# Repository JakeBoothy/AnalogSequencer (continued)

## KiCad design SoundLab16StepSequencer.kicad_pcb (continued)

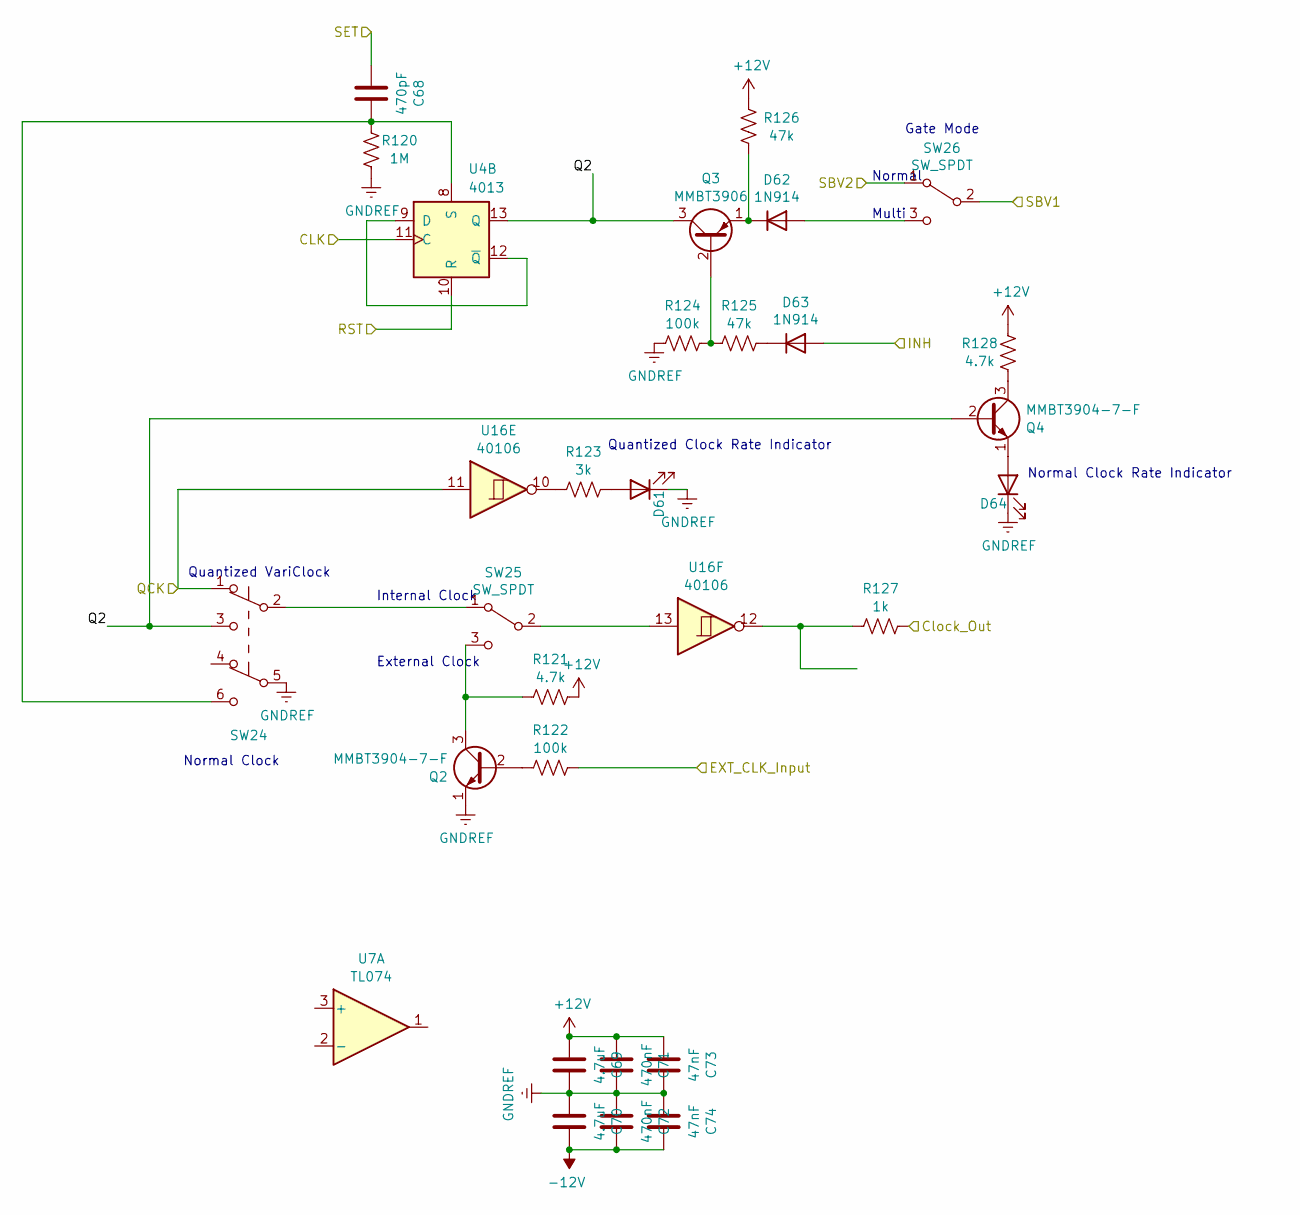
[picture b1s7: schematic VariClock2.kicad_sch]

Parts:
C68: 470pF; C_0603_1608Metric
C69, C70: 4.7uF; C_0805_2012Metric
C71, C72: 470nF; C_0805_2012Metric
C73, C74: 47nF; C_0603_1608Metric
D61, D64: LED; LED_D5.0mm
D62, D63: 1N914; D_SOD-323F
Q2, Q4: MMBT3904-7-F; SOT-23-3
Q3: MMBT3906; SOT-23-3
R120: 1M; R_0603_1608Metric
R121, R128: 4.7k; R_0603_1608Metric
R122, R124: 100k; R_0603_1608Metric
R123: 3k; R_0603_1608Metric
R125, R126: 47k; R_0603_1608Metric
R127: 1k; R_0603_1608Metric
SW24: SW_Push_DPDT; MTS-203-A1-T0
SW25, SW26: SW_SPDT; MTS-103-A01-T0
U4: 4013; SOIC-14_3.9x8.7mm_P1.27mm
U7: TL074; SO-14_3.9x8.65mm_P1.27mm
U16: 40106; SOIC-14_3.9x8.7mm_P1.27mm

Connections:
+12V: C69.2, C71.2, C73.2, R121.2, R126.2, R128.2; also elsewhere on the board
-12V: C70.1, C72.1, C74.1; also elsewhere on the board
/SequencerClocking/X2: D63.2 (A); also elsewhere on the board
/SequencerInput/SBV1: SW26.2 (B); also elsewhere on the board
/SequencerInput/SBV2: SW26.1 (A); also elsewhere on the board
/VariClock1/CLK: U4.11 (C); also elsewhere on the board
/VariClock1/QCK: SW24.1 (A), U16.11; also elsewhere on the board
/VariClock1/RST: U4.10 (R); also elsewhere on the board
/VariClock1/SET: C68.2; also elsewhere on the board
/VariClock2/Clock_Out: R127.2; also elsewhere on the board
/VariClock2/EXT_CLK_Input: R122.2; also elsewhere on the board
/VariClock2/Q2: Q3.3 (C), Q4.2 (B), SW24.3 (C), U4.13 (Q)
GNDREF: C69.1, C70.2, C71.1, C72.2, C73.1, C74.2, D61.1 (K), D64.1 (K), Q2.1 (E), R120.2, R124.1, SW24.5 (B); also elsewhere on the board
unnamed: D61.2 (A), R123.2
unnamed: D62.2 (A), SW26.3 (C)
unnamed: D62.1 (K), Q3.1 (E), R126.1
unnamed: D63.1 (K), R125.2
unnamed: D64.2 (A), Q4.1 (E)
unnamed: Q2.2 (B), R122.1
unnamed: Q2.3 (C), R121.1, SW25.3 (C)
unnamed: Q3.2 (B), R124.2, R125.1
unnamed: Q4.3 (C), R128.1
unnamed: R123.1, U16.10
unnamed: R127.1, U16.12
unnamed: SW24.2 (B), SW25.1 (A)
unnamed: SW25.2 (B), U16.13
unnamed: U4.9 (D), U4.12 (~Q)
unnamed: C68.1, R120.1, SW24.6 (C), U4.8 (S)

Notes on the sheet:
Normal
Normal Clock
Quantized VariClock
External Clock
Quantized Clock Rate Indicator
Normal Clock Rate Indicator
Multi
Gate Mode
Internal Clock

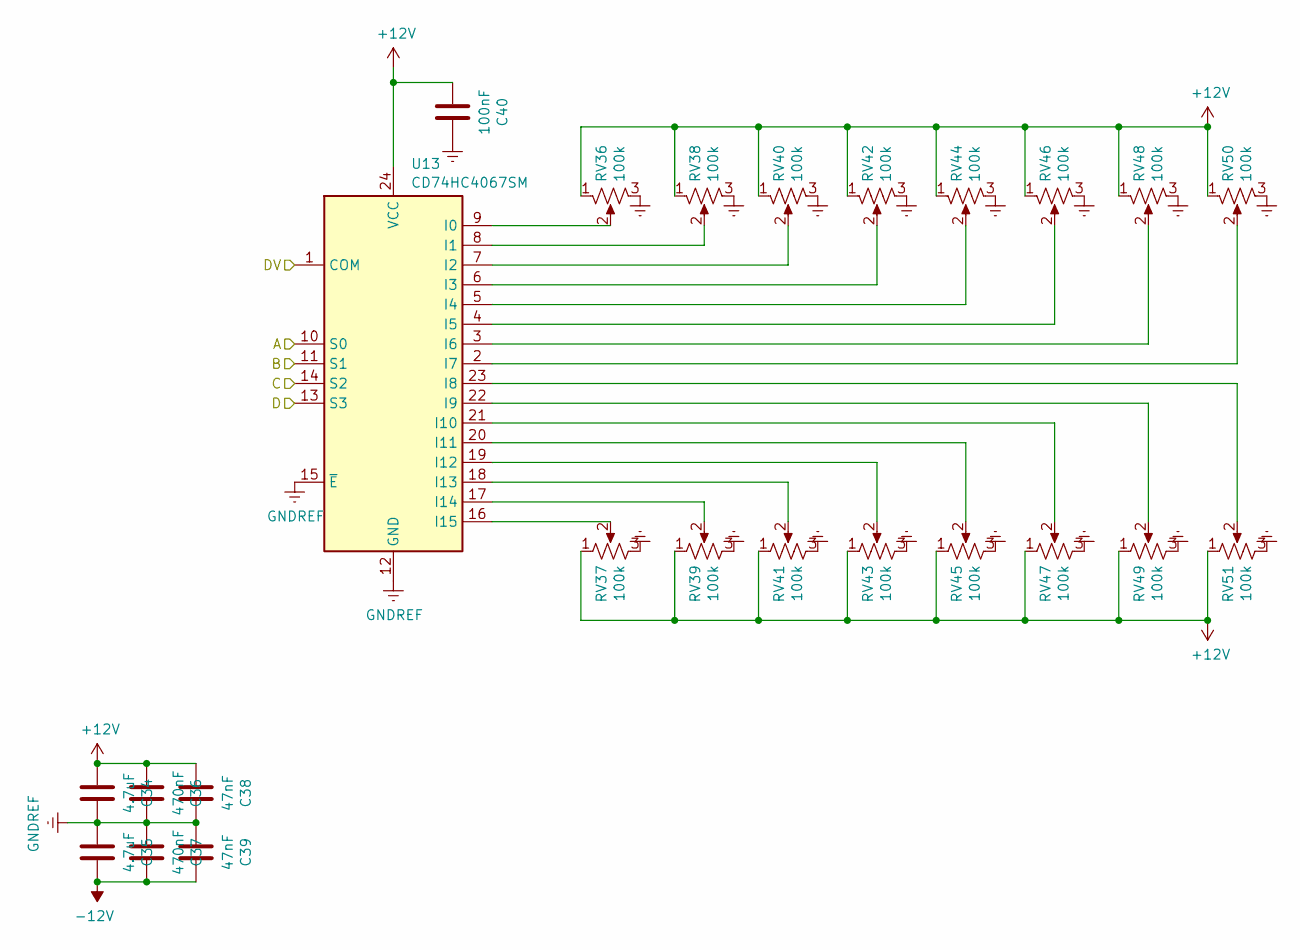
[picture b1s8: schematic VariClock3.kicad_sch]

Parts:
C34, C35: 4.7uF; C_0805_2012Metric
C36, C37: 470nF; C_0805_2012Metric
C38, C39: 47nF; C_0603_1608Metric
C40: 100nF; C_0603_1608Metric
RV36, RV37, RV38, RV39, RV40, RV41, RV42, RV43, RV44, RV45, RV46, RV47, RV48, RV49, RV50, RV51: 100k; Potentiometer_Alps_RK09K_Single_Vertical
U13: CD74HC4067SM; SSOP-24_5.3x8.2mm_P0.65mm

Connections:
+12V: C34.2, C36.2, C38.2, C40.2, RV36.1, RV37.1, RV38.1, RV39.1, RV40.1, RV41.1, RV42.1, RV43.1, RV44.1, RV45.1, RV46.1, RV47.1, RV48.1, RV49.1, RV50.1, RV51.1, U13.24 (VCC); also elsewhere on the board
-12V: C35.1, C37.1, C39.1; also elsewhere on the board
/SequencerAnalogGenerator/QA: U13.10 (S0); also elsewhere on the board
/SequencerAnalogGenerator/QB: U13.11 (S1); also elsewhere on the board
/SequencerAnalogGenerator/QC: U13.14 (S2); also elsewhere on the board
/SequencerAnalogGenerator/QD: U13.13 (S3); also elsewhere on the board
/VariClock1/DV: U13.1 (COM); also elsewhere on the board
GNDREF: C34.1, C35.2, C36.1, C37.2, C38.1, C39.2, C40.1, RV36.3, RV37.3, RV38.3, RV39.3, RV40.3, RV41.3, RV42.3, RV43.3, RV44.3, RV45.3, RV46.3, RV47.3, RV48.3, RV49.3, RV50.3, RV51.3, U13.12 (GND), U13.15 (~E); also elsewhere on the board
unnamed: RV36.2, U13.9 (I0)
unnamed: RV38.2, U13.8 (I1)
unnamed: RV40.2, U13.7 (I2)
unnamed: RV42.2, U13.6 (I3)
unnamed: RV44.2, U13.5 (I4)
unnamed: RV46.2, U13.4 (I5)
unnamed: RV48.2, U13.3 (I6)
unnamed: RV50.2, U13.2 (I7)
unnamed: RV51.2, U13.23 (I8)
unnamed: RV49.2, U13.22 (I9)
unnamed: RV47.2, U13.21 (I10)
unnamed: RV45.2, U13.20 (I11)
unnamed: RV43.2, U13.19 (I12)
unnamed: RV41.2, U13.18 (I13)
unnamed: RV39.2, U13.17 (I14)
unnamed: RV37.2, U13.16 (I15)

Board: 2 copper layers, 366 parts (1 on the bottom side), 260 nets, no tracks yet.

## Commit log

2023-12-03 init commit
2023-12-21 created pcb file, placed parts
2023-12-24 init placement/layout
2023-12-25 routing and placing
2023-12-26 routed 100%
2023-12-27 added manufacturing files for v1
2023-12-27 Created schematic files.
2023-12-28 jlc files
2024-01-01 lots of work... created faceplate
2024-01-02 manufacturing files for faceplate...
2024-01-02 switched files around... fixed mistake
2024-01-04 face plate mods...
